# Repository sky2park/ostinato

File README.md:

# Ostinato

[🇺🇸 English](docs/README.en.md)

처음부터 직접 설계한 40% 오소리니어 기계식 키보드입니다.

Ostinato는 커스텀 PCB, 알루미늄 케이스, 가스켓 마운트 플레이트, 로터리 엔코더, RGB 상태 표시등, USB 연결을 기본으로 하는 45키 오소리니어 키보드입니다. USB 전원이 공급되는 상태에서 Bluetooth 무선 출력을 사용할 수 있습니다.

이 프로젝트에는 PCB와 케이스부터 QMK/Vial 펌웨어와 ESP32-C3 Bluetooth 컨트롤러까지 전체 하드웨어 및 펌웨어 설계가 포함되어 있습니다.

---

## 주요 기능

- 40% 오소리니어 레이아웃
- 45키
- MX 호환 스위치
- QMK 펌웨어
- Vial 지원
- USB 및 Bluetooth 연결
- ESP32-C3 기반 Bluetooth 컨트롤러 (USB 전원 필요, 배터리 없음, 단독 무선 작동 불가)
- RP2040 기반 메인 컨트롤러
- 3개의 Bluetooth 연결 슬롯
- 로터리 엔코더
- SK6812MINI RGB LED
- 전용 Bluetooth 상태 표시등
- 레이어 상태 표시
- 가스켓 마운트 플레이트
- 커스텀 알루미늄 상판 케이스
- MJF PA12S 나일론 하판 케이스
- SUS304 스테인리스 스틸 또는 H59 구리 합금 황동 내부 웨이트

---

## 사양

| 항목 | 내용 |
|---|---|
| 레이아웃 | 40% 오소리니어 |
| 키 수 | 45 |
| 메인 MCU | RP2040 |
| Bluetooth MCU | ESP32-C3 |
| 펌웨어 | QMK |
| 키맵 설정 | Vial |
| 연결 방식 | USB 기본 / Bluetooth 무선 출력 (USB 전원 필요) |
| 전원 공급 | USB |
| 배터리 | 없음 |
| Bluetooth 슬롯 | 3 |
| 스위치 종류 | MX 호환 |
| RGB LED | SK6812MINI (4개) |
| 로터리 엔코더 | 1개 |
| 마운팅 | 가스켓 마운트 (Poron) |
| 플레이트 | PC |
| 상판 케이스 | 6061 알루미늄 |
| 하판 케이스 | MJF PA12S 나일론 |
| 내부 웨이트 | SUS304 스테인리스 스틸 또는 H59 구리 합금 황동 |

---

## 레이아웃

Ostinato는 45키의 컴팩트한 40% 오소리니어 레이아웃을 사용합니다.

작은 크기를 유지하면서 풀사이즈 키보드에 준하는 기능을 제공할 수 있도록 여러 레이어를 중심으로 설계되었습니다.

### 레이어

펌웨어에는 다음과 같은 주요 레이어가 포함되어 있습니다:

- **기본**
- **내비게이션**
- **숫자 / 기호**
- **기능**
- **게이밍**
- **게이밍+**
- **게이밍 내비게이션**

추가 레이어와 키 할당은 Vial을 통해 설정할 수 있습니다.

---

## 연결

Ostinato는 USB 연결을 기본으로 사용하며, USB 전원이 공급되는 상태에서 Bluetooth 무선 출력을 지원합니다.

> **⚠️ 전원 및 Bluetooth 사용 안내**
>
> Ostinato는 배터리를 내장하지 않은 키보드입니다. 키보드의 작동과 Bluetooth 사용을 위해 USB 케이블을 연결해야 합니다.
>
> USB 케이블을 연결하지 않은 상태에서는 키보드 단독으로 Bluetooth를 사용할 수 없습니다.

RP2040은 키보드의 주요 기능을 담당하며, ESP32-C3 모듈이 Bluetooth 연결을 제공합니다.

### USB

USB 모드에서는 일반적인 USB HID 키보드로 동작합니다.

### Bluetooth

키보드는 3개의 Bluetooth 연결 슬롯을 지원합니다:

- **Bluetooth 1**
- **Bluetooth 2**
- **Bluetooth 3**

활성 Bluetooth 슬롯은 키보드에서 직접 선택할 수 있습니다. 펌웨어는 UART를 통해 ESP32-C3와 통신하며 Bluetooth 연결 상태와 슬롯 선택을 제어합니다.

Bluetooth를 사용하더라도 USB 케이블을 통한 전원 공급이 필요합니다. 배터리가 없으므로 USB 전원 없이 Bluetooth만으로 작동할 수 없습니다.

---

## Bluetooth 상태

RGB LED는 Bluetooth 상태를 시각적으로 표시하는 데 사용됩니다. 각 Bluetooth 슬롯에는 전용 상태 표시등이 있습니다.

표시등은 다음과 같은 상태를 구분합니다:

- 광고(Advertising)
- 연결됨
- 페어링
- 오류 / 사용 불가

이를 통해 호스트 기기를 사용하지 않고도 현재 Bluetooth 연결 상태를 확인할 수 있습니다.

---

## RGB 표시등

Ostinato는 4개의 SK6812MINI RGB LED를 사용합니다. 이 LED는 장식용 백라이트가 아니라 기능적인 상태 표시등으로 사용됩니다.

### Bluetooth 표시등

3개의 LED가 각각 3개의 Bluetooth 슬롯 상태를 표시합니다.

### 레이어 표시등

나머지 1개의 LED는 레이어/상태 표시용으로 사용됩니다. 펌웨어는 이 표시등을 특수 키보드 기능의 상태를 표시하는 데에도 사용할 수 있습니다.

---

## 로터리 엔코더

Ostinato에는 추가 입력을 위한 로터리 엔코더가 포함되어 있습니다.

엔코더는 QMK와 Vial을 통해 설정할 수 있으며, 활성 레이어에 따라 서로 다른 기능을 할당할 수 있습니다.

---

## 아키텍처 및 설계 철학

Ostinato의 목표는 컴팩트한 오소리니어 레이아웃에 일반적으로 대형 키보드에서 제공되는 기능을 결합하는 것입니다.

하나의 무선 컨트롤러에 모든 기능을 의존하는 대신, 메인 키보드 컨트롤러와 Bluetooth 컨트롤러를 분리하는 구조로 설계했습니다:

```text
       ┌───────────────┐
       │    RP2040     │
       │ Main Keyboard │
       │  Controller   │
       └───────┬───────┘
               │
              UART
               │
       ┌───────▼───────┐
       │   ESP32-C3    │
       │   Bluetooth   │
       │  Controller   │
       └───────────────┘
```

이 아키텍처를 통해 RP2040은 핵심 키보드 동작(매트릭스 스캔, 조명, Vial 설정)을 담당하고, ESP32-C3는 Bluetooth 연결 스택을 담당합니다.

---

## 펌웨어

Ostinato 펌웨어는 QMK 및 Vial-QMK를 기반으로 하며 **GNU General Public License v2.0 (GPL-2.0)**에 따라 라이선스가 부여됩니다.

```text
firmware/
├── esp32-c3/
├── qmk/
│   └── ostinato/
└── vial/
    └── ostinato/
```

- **QMK 펌웨어**: 매트릭스 스캔, 키맵 및 레이어, 커스텀 키코드, 로터리 엔코더, RGB 상태 표시등, USB 출력, ESP32-C3와의 UART 통신을 담당합니다.
- **ESP32-C3 펌웨어**: Bluetooth 프로파일 관리, 연결 슬롯, 무선 HID 출력을 담당합니다.

### 커스텀 키코드

Ostinato는 출력 및 연결 제어를 위해 다음과 같은 커스텀 키코드를 정의합니다:

- `OUT_USB`
- `OUT_BT1`
- `OUT_BT2`
- `OUT_BT3`
- `BT_CLR`

이 키코드를 사용하면 USB와 페어링된 3개의 Bluetooth 기기 사이를 즉시 전환할 수 있습니다.

---

## 하드웨어

PCB, 케이스, 플레이트 및 관련 CAD 파일을 포함한 Ostinato 하드웨어 설계 파일은 **Creative Commons Attribution-NonCommercial 4.0 International (CC BY-NC 4.0)** 라이선스에 따라 제공됩니다.

개인적 및 비상업적 사용은 허용됩니다.

상업적 사용에는 저작자의 사전 허가가 필요합니다.

하드웨어는 다음과 같은 모듈형 커스텀 보드로 구성됩니다:

```text
pcb/
├── main-module/
├── led_module/
└── knob-module/
```

- **메인 모듈**: RP2040 컨트롤러, ESP32-C3, 다이오드 매트릭스 및 전원 회로를 탑재합니다.
- **LED 모듈**: 슬롯 및 레이어 상태 표시를 위한 4개의 SK6812MINI 어드레서블 RGB LED를 탑재합니다.
- **노브 모듈**: 로터리 엔코더와 브레이크아웃 인터페이스를 탑재합니다.

### 케이스 및 플레이트

- **상판 케이스**: CNC 가공 6061 알루미늄
- **하판 케이스**: MJF 3D 프린팅 PA12S 나일론
- **내부 웨이트**: 레이저 절단 SUS304 스테인리스 스틸 또는 H59 구리 합금 황동
- **마운팅**: PC 플레이트를 분리하는 커스텀 Poron 가스켓 스트립을 사용하여 부드럽고 공명감 있는 바텀아웃을 구현합니다.

> **제조 및 공차 관련 참고사항**  
> 모든 케이스 부품(상판 케이스, 하판 케이스, 내부 웨이트)은 **JLCCNC** 및 **JLC3DP**를 통해 프로토타입을 제작하고 검증했습니다. 제조업체와 제작 방식에 따라 공차와 표면 마감이 달라질 수 있으므로, 다른 업체에서 제작한 부품은 테스트되지 않았으며 조립 또는 치수 호환성 문제가 발생할 수 있습니다.

플레이트 절단 프로파일은 `plate/` 아래에 DXF 형식으로 제공됩니다:
- `design.dxf`
- `plate.dxf`

---

## 제조 및 주문 가이드

모든 부품은 특정 제작 업체를 기준으로 설계하고 검증했습니다. Ostinato를 제작할 계획이라면 아래 주문 가이드를 참고하세요.

### 개요

| 부품 | 소스 파일 | 권장 서비스 | 공정 / 재료 사양 |
|---|---|---|---|
| **Top Case** | `case/top.step`<br>`case/top_theads.pdf` (Thread/tapping drawing) | JLCCNC | CNC Machining / 6061 Aluminum (Sandblasted / Anodized) |
| **Bottom Case** | `case/bottom.step` | JLC3DP | 3D Printing / MJF Nylon (PA12S) |
| **Internal Weight** | `case/weight.step` | JLCCNC | CNC or Sheet Metal / SUS304 Stainless steel or H59 Brass |
| **Plate** | `plate/plate.dxf` | Laser cutting service | Laser Cut / 1.5mm Polycarbonate (PC) |
| **PCBs** | `pcb/*/gerber/` | JLCPCB | FR-4 / 1.6mm (or 1.2mm depending on build) |

---

### 부품 상세 및 주문 방법

#### 1. 케이스 및 웨이트 (JLCCNC / JLC3DP)
- **Top Case**:
  - **File**: `case/top.step`
  - **나사산 도면**: `case/top_theads.pdf` (탭 가공을 주문할 때 이 2D 도면을 함께 첨부하세요)
  - **서비스**: [JLCCNC](https://jlccnc.com/) (CNC 가공)
  - **재료**: 6061 알루미늄
  - **표면 처리**: 비드 블라스트(샌드블라스트 #150 또는 #180) + 아노다이징(원하는 색상)
- **Bottom Case**:
  - **File**: `case/bottom.step`
  - **Service**: [JLC3DP](https://jlc3dp.com/) (3D Printing)
  - **기술**: MJF (Multi Jet Fusion)
  - **재료**: PA12S 나일론 (검정/염색)
- **Internal Weight**:
  - **File**: `case/weight.step`
  - **Service**: [JLCCNC](https://jlccnc.com/)
  - **재료**: SUS304 스테인리스 스틸 (헤어라인 / 샌드블라스트) 또는 H59 황동

> ⚠️ **중요 공차 경고**:  
> CAD 모델, 공차 및 조립 여유 치수는 **JLCCNC** 및 **JLC3DP**를 기준으로 조정하고 검증했습니다. 다른 업체나 다른 제작 방식은 테스트되지 않았으며, 부적절한 조립, 수축 편차 또는 조립 문제가 발생할 수 있습니다.

#### 2. 스위치 플레이트
- **File**: `plate/plate.dxf`
- **재료**: 1.5mm 폴리카보네이트 (PC)
- **서비스**: 정밀 레이저 절단이 가능한 업체 (예: JLCCNC 판재 절단 또는 현지 레이저 절단 업체).

#### 3. PCB
- **Paths**:
  - `pcb/main-module/`
  - `pcb/led_module/`
  - `pcb/knob-module/`
- **Service**: [JLCPCB](https://jlcpcb.com/)
- **Ordering Recommendations**:
  - Upload the Gerber zip files along with the **BOM and CPL files** from each folder to order the **PCB Assembly (SMT)** service.
  - **PCBA Settings**:
    - **Assembly Side**: Select **`Bottom Side`** for all three modules.
    - **PCBA Type**:
      - `main-module`: Must be set to **`Standard`** due to assembly constraints of the ESP32-C3 module (bottom pad soldering).
      - `led_module` & `knob-module`: Select **`Economy`**.
  - ⚠️ **Note**: The **EC11 rotary encoder** on the `knob-module` is not covered by the SMT service; source it separately and solder it by hand (through-hole soldering).
  
#### 4. 추가 기성 부품 (하드웨어 및 구매)

이러한 표준 하드웨어 부품과 구성품은 별도 제작품이 아니며, 일반 하드웨어 마켓플레이스(예: AliExpress)나 커스텀 키보드 판매처에서 구매할 수 있습니다.

> **참고**: 아래 링크는 제가 프로토타입 제작에 실제로 사용한 동일한 제품 목록과 구매처입니다. 참고용으로만 제공하며, 사양에 맞는 동등한 부품이라면 어떤 제품을 사용해도 됩니다.

| 품목 | 사양 | 수량 | 참고 링크 | 비고 |
|---|---|---|---|---|
| **Poron Gasket Strips** | 20mm (L) × 3mm (W) × 2mm (T) | 8 | [AliExpress](https://ko.aliexpress.com/item/1005005713921230.html) | Mounts to plate tabs / case edges |
| **FPC Ribbon Cable** | 0.5mm pitch, 6-pin, **Reverse (Type B)**, 10–15cm | 2 | [AliExpress](https://aliexpress.com/item/1005007862185591.html) | Connects main module to LED / knob modules |
| **Rotary Encoder** | EC11 rotary encoder, **15mm shaft height** | 1 | [AliExpress](https://aliexpress.com/item/1005009120433387.html) | Hand-soldered onto `knob-module` |
| **Encoder Knob** | Compatible with EC11 shaft **20 x 13 x 6mm** | 1 | [AliExpress](https://aliexpress.com/item/1005007339301144.html) | Fits selected rotary encoder |
| **Unified Daughterboard S1 & Cable** | Unified Daughterboard (UDB) S1 with Molex cable | 1 | [Vendor Link](https://keebd.com/products/unified-daughterboards?variant=45606739411096) | Available via various keyboard vendor stores (e.g., CannonKeys, Swagkeys, etc.)
| **Light Guides** | Acrylic light pipe / guide **1.5-2.2 or 2.9-3.0** | 4 | [AliExpress](https://aliexpress.com/item/1005005231503928.html) | Diffuses status LEDs |
| **Heat-set Insert** | M2 × L3mm × OD 3.2mm | 4 | [AliExpress](https://aliexpress.com/item/1005006472641726.html) | Case / module mounting |
| **Heat-set Insert** | M3 × L4mm × OD 4.2mm | 6 | [AliExpress](https://aliexpress.com/item/1005006472641726.html) | Weight / case and Weight / UDB mounting |
| **Screw** | M2 × 4mm | 4 | [AliExpress](https://aliexpress.com/item/1005005270702287.html) | Internal module mounting |
| **Screw** | M2.5 × 8mm | 4 | [AliExpress](https://aliexpress.com/item/1005005270702287.html) | Case assembly |
| **Screw** | M3 × 5mm | 6 | [AliExpress](https://aliexpress.com/item/1005005270702287.html) | Internal weight / UDB fastening |

---

## 빌드 가이드

🚧 상세 빌드 가이드 영상은 현재 준비 중입니다.

---

## 저장소 구조

```text
ostinato/
├── case/             # CAD and step/stl files for case parts
├── firmware/
│   ├── esp32-c3/     # ESP-IDF / Arduino BT firmware
│   ├── qmk/          # QMK source and keyboard rules
│   │   └── ostinato/
│   └── vial/         # Vial configuration & keymap files
│       └── ostinato/
├── pcb/
│   ├── main-module/  # Schematic, KiCad layouts, and Gerber files
│   ├── led_module/
│   └── knob-module/
├── plate/
│   ├── design.dxf
│   └── plate.dxf
└── README.md
```

---

## 상태

Ostinato는 현재 개발이 진행 중인 커스텀 하드웨어 프로젝트입니다. 실제 리비전을 테스트하는 과정에서 회로도, Gerber 파일 및 펌웨어 구현이 호환성을 깨뜨리는 형태로 변경될 수 있습니다.

---

## 크레딧

**sky2park**가 설계 및 개발했습니다.

- [QMK Firmware](https://qmk.fm/)
- [Vial](https://get.vial.today/)
- Raspberry Pi RP2040 & Espressif ESP32-C3

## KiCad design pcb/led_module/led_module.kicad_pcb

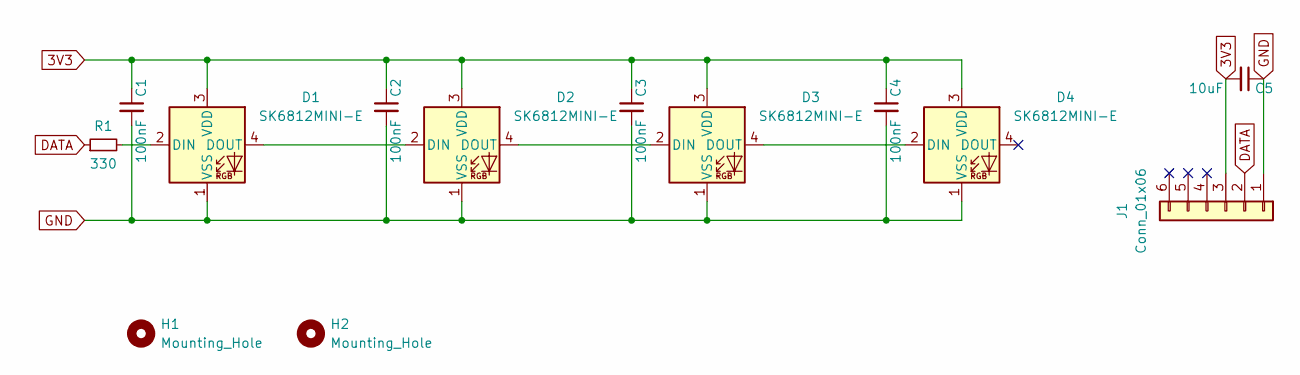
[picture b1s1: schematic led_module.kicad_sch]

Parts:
C1, C2, C3, C4: 100nF; C_0402_1005Metric; LCSC C66501
C5: 10uF; C_0402_1005Metric; LCSC C66501
D1, D2, D3, D4: SK6812MINI-E; LED_SK6812MINI-E_3.2x2.8mm_P1.5mm_ReverseMount
H1, H2: Mounting_Hole; Standoff_M2x6mm
J1: Conn_01x06; Hirose_FH12-6S-0.5SH_1x06-1MP_P0.50mm_Horizontal
R1: 330; R_0402_1005Metric; LCSC C21190

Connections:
3V3: C1.1, C2.1, C3.1, C4.1, C5.2, D1.3 (VDD), D2.3 (VDD), D3.3 (VDD), D4.3 (VDD), J1.3
DATA: J1.2, R1.1
GND: C1.2, C2.2, C3.2, C4.2, C5.1, D1.1 (VSS), D2.1 (VSS), D3.1 (VSS), D4.1 (VSS), J1.1
unnamed: D1.2 (DIN), R1.2
unnamed: D1.4 (DOUT), D2.2 (DIN)
unnamed: D2.4 (DOUT), D3.2 (DIN)
unnamed: D3.4 (DOUT), D4.2 (DIN)

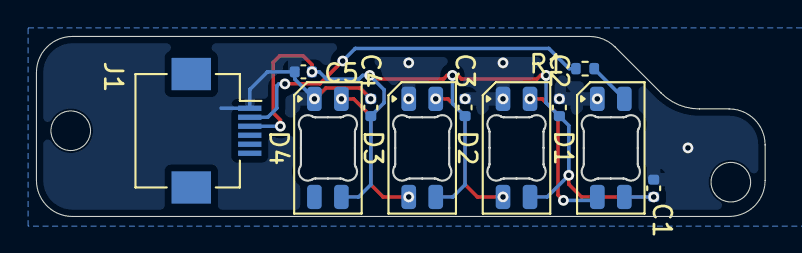
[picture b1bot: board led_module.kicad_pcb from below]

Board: 2 copper layers, 40.5 x 10.0 mm, 13 parts (11 on the bottom side), 7 nets.

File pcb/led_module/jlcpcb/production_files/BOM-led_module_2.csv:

Comment,Designator,Footprint,LCSC,Quantity
100nF,"C1,C2,C3,C4",C_0402_1005Metric,C1525,4
10uF,C5,C_0402_1005Metric,C15525,1
330,R1,R_0402_1005Metric,C21190,1
Conn_01x06,J1,Hirose_FH12-6S-0.5SH_1x06-1MP_P0.50mm_Horizontal,C202118,1
SK6812MINI-E,"D1,D2,D3,D4",LED_SK6812MINI-E_3.2x2.8mm_P1.5mm_ReverseMount,C5378731,4

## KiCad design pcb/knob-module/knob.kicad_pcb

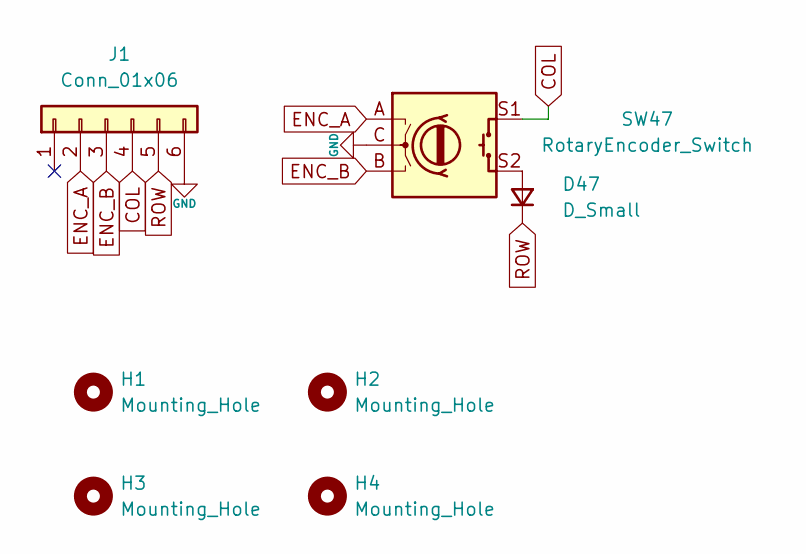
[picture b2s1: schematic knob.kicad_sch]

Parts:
D47: D_Small; D_SOD-123
H1, H2, H3, H4: Mounting_Hole; Standoff_M2x6mm
J1: Conn_01x06; Hirose_FH12-6S-0.5SH_1x06-1MP_P0.50mm_Horizontal
SW47: RotaryEncoder_Switch; Encoder_EC11_MX

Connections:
COL: J1.4, SW47.S1
ENC_A: J1.2, SW47.A
ENC_B: J1.3, SW47.B
GND: J1.6, SW47.C
unnamed: D47.2 (A), SW47.S2
ROW: D47.1 (K), J1.5

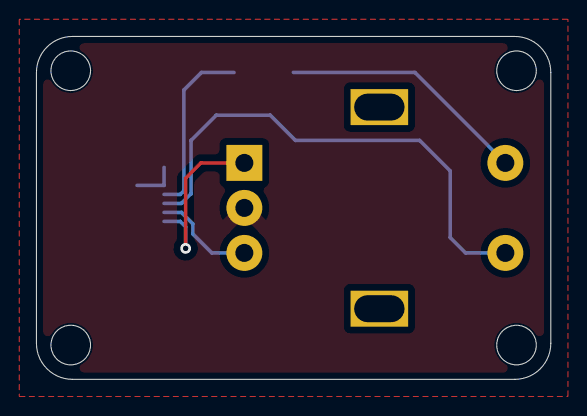
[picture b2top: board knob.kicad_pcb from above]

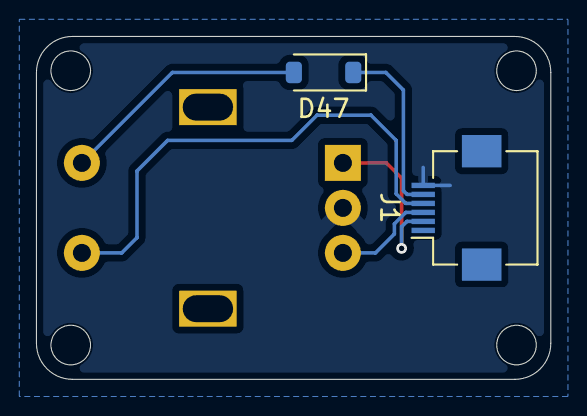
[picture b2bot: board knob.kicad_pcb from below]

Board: 2 copper layers, 28.6 x 19.1 mm, 7 parts (2 on the bottom side), 6 nets.

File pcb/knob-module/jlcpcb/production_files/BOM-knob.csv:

Comment,Designator,Footprint,LCSC,Quantity
Conn_01x06,J1,Hirose_FH12-6S-0.5SH_1x06-1MP_P0.50mm_Horizontal,C202118,1
D_Small,D47,D_SOD-123,C81598,1

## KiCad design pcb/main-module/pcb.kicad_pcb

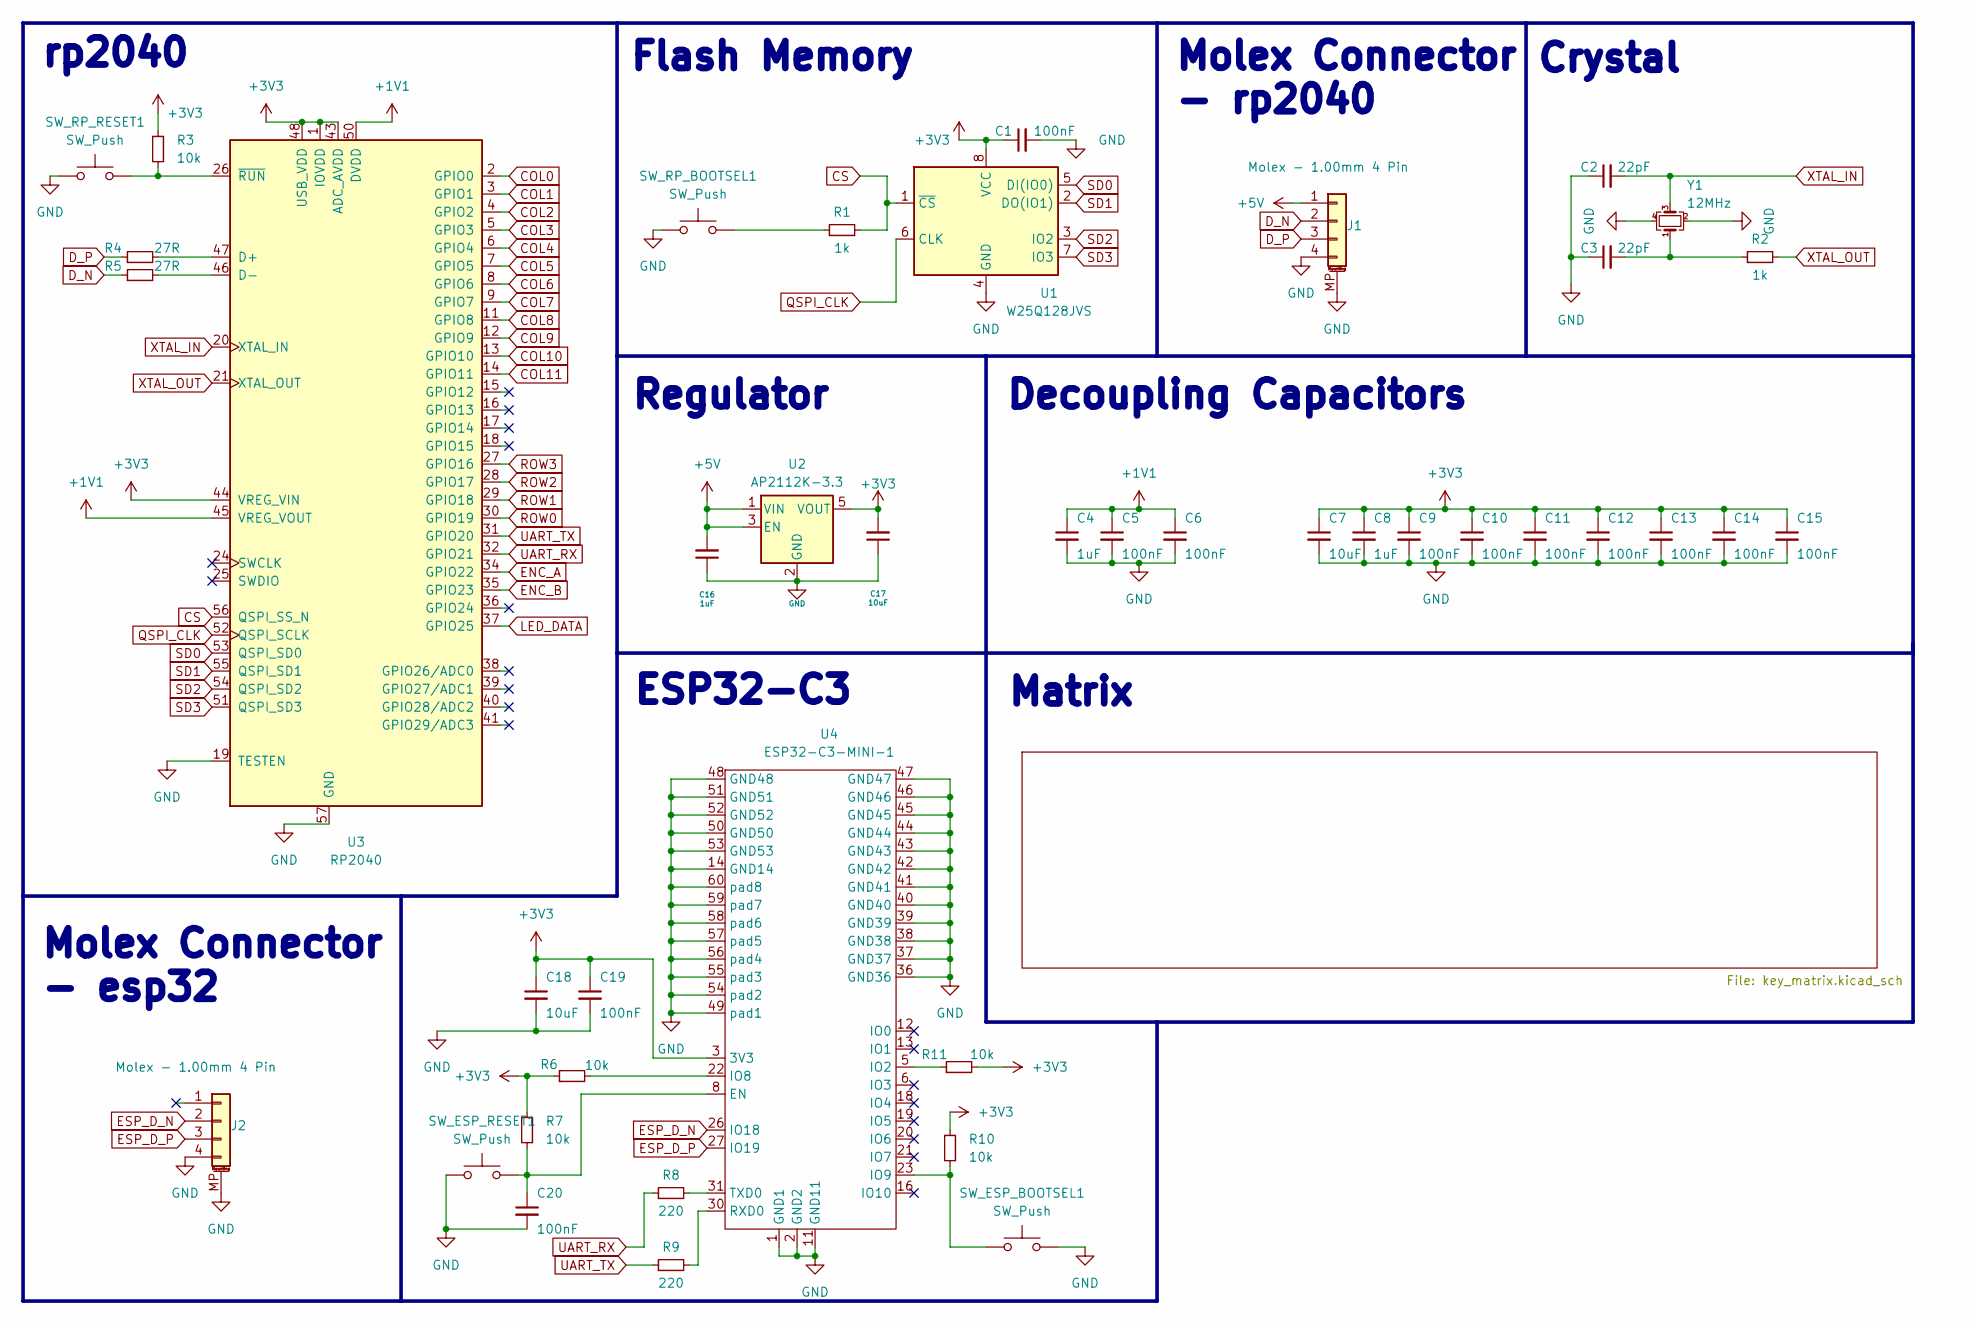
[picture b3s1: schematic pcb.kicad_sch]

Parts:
C1, C5, C6, C9, C10, C11, C12, C13, C14, C15: 100nF; C_0402_1005Metric; LCSC C66501
C2, C3: 22pF; C_0402_1005Metric; LCSC C1653
C4, C8, C16: 1uF; C_0402_1005Metric; LCSC C5673
C7: 10uF; C_0402_1005Metric; LCSC C1691
C17: 10uF; C_0402_1005Metric; LCSC C19702
C18: 10uF; C_0402_1005Metric; LCSC C15525
C19, C20: 100nF; C_0402_1005Metric; LCSC C1525
J1: Molex - 1.00mm 4 Pin; Molex_Pico-EZmate_78171-0004_1x04-1MP_P1.20mm_Vertical; LCSC C588524
J2: Molex - 1.00mm 4 Pin; Molex_Pico-EZmate_78171-0004_1x04-1MP_P1.20mm_Vertical; LCSC C160404
R1, R2: 1k; R_0402_1005Metric; LCSC C21190
R3: 10k; R_0402_1005Metric; LCSC C25804
R4, R5: 27R; R_0402_1005Metric; LCSC C25190
R6, R7, R10, R11: 10k; R_0402_1005Metric; LCSC C11702
R8, R9: 220; R_0402_1005Metric
SW_ESP_BOOTSEL1: SW_Push; SW_SPST_TS-1088-xR020
SW_ESP_RESET1: SW_Push; SW_SPST_TS-1088-xR020
SW_RP_BOOTSEL1: SW_Push; SW_SPST_TS-1088-xR020
SW_RP_RESET1: SW_Push; SW_SPST_TS-1088-xR020
U1: W25Q128JVS; SOIC-8_5.3x5.3mm_P1.27mm; LCSC C131025
U2: AP2112K-3.3; SOT-23-5
U3: RP2040; RP2040-QFN-56; LCSC C2040
U4: ESP32-C3-MINI-1; LCSC C41349510
Y1: 12MHz; Crystal_SMD_3225-4Pin_3.2x2.5mm; LCSC C9002

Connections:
+1V1: C4.1, C5.1, C6.1, U3.23 (DVDD), U3.45 (VREG_VOUT), U3.50 (DVDD)
+3V3: C1.1, C7.1, C8.1, C9.1, C10.1, C11.1, C12.1, C13.1, C14.1, C15.1, C17.2, C18.1, C19.1, R3.1, R6.1, R7.1, R10.1, R11.2, U1.8 (VCC), U2.5 (VOUT), U3.1 (IOVDD), U3.10 (IOVDD), U3.22 (IOVDD), U3.33 (IOVDD), U3.42 (IOVDD), U3.43 (ADC_AVDD), U3.44 (VREG_VIN), U3.48 (USB_VDD), U3.49 (IOVDD), U4.3 (3V3); also elsewhere on the board
+5V: C16.2, J1.1, U2.1 (VIN), U2.3 (EN)
COL0: U3.2 (GPIO0); also elsewhere on the board
COL1: U3.3 (GPIO1); also elsewhere on the board
COL2: U3.4 (GPIO2); also elsewhere on the board
COL3: U3.5 (GPIO3); also elsewhere on the board
COL4: U3.6 (GPIO4); also elsewhere on the board
COL5: U3.7 (GPIO5); also elsewhere on the board
COL6: U3.8 (GPIO6); also elsewhere on the board
COL7: U3.9 (GPIO7); also elsewhere on the board
COL8: U3.11 (GPIO8); also elsewhere on the board
COL9: U3.12 (GPIO9); also elsewhere on the board
COL10: U3.13 (GPIO10); also elsewhere on the board
COL11: U3.14 (GPIO11); also elsewhere on the board
CS: R1.2, U1.1 (~CS), U3.56 (QSPI_SS_N)
D_N: J1.2, R5.1
D_P: J1.3, R4.1
ENC_A: U3.34 (GPIO22); also elsewhere on the board
ENC_B: U3.35 (GPIO23); also elsewhere on the board
ESP_D_N: J2.2, U4.26 (IO18)
ESP_D_P: J2.3, U4.27 (IO19)
GND: C1.2, C2.1, C3.1, C4.2, C5.2, C6.2, C7.2, C8.2, C9.2, C10.2, C11.2, C12.2, C13.2, C14.2, C15.2, C16.1, C17.1, C18.2, C19.2, C20.2, J1.4, J1.MP (MountPin), J2.4, J2.MP (MountPin), SW_ESP_BOOTSEL1.2, SW_ESP_RESET1.1, SW_RP_BOOTSEL1.1, SW_RP_RESET1.1, U1.4 (GND), U2.2 (GND), U3.19 (TESTEN), U3.57 (GND), U4.1 (GND1), U4.2 (GND2), U4.11 (GND11), U4.14 (GND14), U4.36 (GND36), U4.37 (GND37), U4.38 (GND38), U4.39 (GND39), U4.40 (GND40), U4.41 (GND41), U4.42 (GND42), U4.43 (GND43), U4.44 (GND44), U4.45 (GND45), U4.46 (GND46), U4.47 (GND47), U4.48 (GND48), U4.49 (pad1), U4.50 (GND50), U4.51 (GND51), U4.52 (GND52), U4.53 (GND53), U4.54 (pad2), U4.55 (pad3), U4.56 (pad4), U4.57 (pad5), U4.58 (pad6), U4.59 (pad7), U4.60 (pad8), Y1.2, Y1.4; also elsewhere on the board
LED_DATA: U3.37 (GPIO25); also elsewhere on the board
unnamed: C3.2, R2.1, Y1.1
unnamed: R1.1, SW_RP_BOOTSEL1.2
unnamed: R4.2, U3.47 (D+)
unnamed: R5.2, U3.46 (D-)
unnamed: R3.2, SW_RP_RESET1.2, U3.26 (~RUN)
unnamed: C20.1, R7.2, SW_ESP_RESET1.2, U4.8 (EN)
unnamed: R11.1, U4.5 (IO2)
unnamed: R6.2, U4.22 (IO8)
unnamed: R10.2, SW_ESP_BOOTSEL1.1, U4.23 (IO9)
unnamed: R9.2, U4.30 (RXD0)
unnamed: R8.2, U4.31 (TXD0)
QSPI_CLK: U1.6 (CLK), U3.52 (QSPI_SCLK)
ROW0: U3.30 (GPIO19); also elsewhere on the board
ROW1: U3.29 (GPIO18); also elsewhere on the board
ROW2: U3.28 (GPIO17); also elsewhere on the board
ROW3: U3.27 (GPIO16); also elsewhere on the board
SD0: U1.5 (DI(IO0)), U3.53 (QSPI_SD0)
SD1: U1.2 (DO(IO1)), U3.55 (QSPI_SD1)
SD2: U1.3 (IO2), U3.54 (QSPI_SD2)
SD3: U1.7 (IO3), U3.51 (QSPI_SD3)
UART_RX: R8.1, U3.32 (GPIO21)
UART_TX: R9.1, U3.31 (GPIO20)
XTAL_IN: C2.2, U3.20 (XTAL_IN), Y1.3
XTAL_OUT: R2.2, U3.21 (XTAL_OUT)

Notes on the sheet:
Molex Connector - rp2040
Decoupling Capacitors
Regulator
rp2040
Crystal
ESP32-C3
Molex Connector - esp32
Flash Memory
Matrix

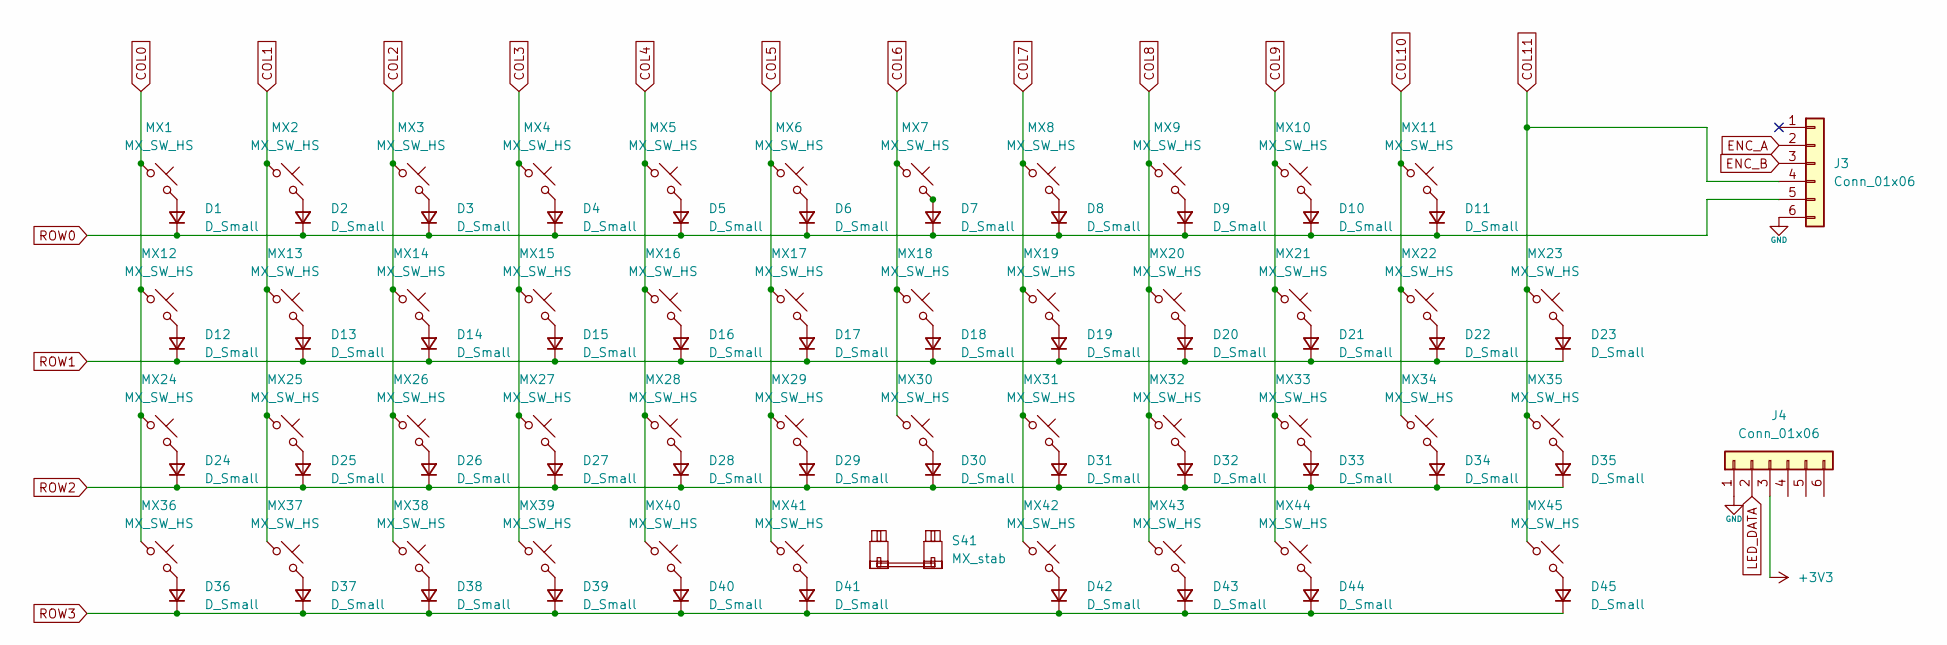
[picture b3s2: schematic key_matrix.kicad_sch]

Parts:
D1, D2, D3, D4, D5, D6, D7, D8, D9, D10, D11, D12, D13, D14, D15, D16, D17, D18, D19, D20, D21, D22, D23, D24, D25, D26, D27, D28, D29, D30, D31, D32, D33, D34, D35, D36, D37, D38, D39, D40, D41, D42, D43, D44, D45: D_Small; D_SOD-123
J3, J4: Conn_01x06; Hirose_FH12-6S-0.5SH_1x06-1MP_P0.50mm_Horizontal
MX1, MX2, MX3, MX4, MX5, MX6, MX7, MX8, MX9, MX10, MX11, MX12, MX13, MX14, MX15, MX16, MX17, MX18, MX19, MX20, MX21, MX22, MX23, MX24, MX25, MX26, MX27, MX28, MX29, MX30, MX31, MX32, MX33, MX34, MX35, MX36, MX37, MX38, MX39, MX40, MX41, MX42, MX43, MX44, MX45: MX_SW_HS; SW_MX_HS_CPG151101S11_1u
S41: MX_stab; STAB_MX_P_2u

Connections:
+3V3: J4.3; also elsewhere on the board
COL0: MX1.1, MX12.1, MX24.1, MX36.1; also elsewhere on the board
COL1: MX2.1, MX13.1, MX25.1, MX37.1; also elsewhere on the board
COL2: MX3.1, MX14.1, MX26.1, MX38.1; also elsewhere on the board
COL3: MX4.1, MX15.1, MX27.1, MX39.1; also elsewhere on the board
COL4: MX5.1, MX16.1, MX28.1, MX40.1; also elsewhere on the board
COL5: MX6.1, MX17.1, MX29.1, MX41.1; also elsewhere on the board
COL6: MX7.1, MX18.1, MX30.1; also elsewhere on the board
COL7: MX8.1, MX19.1, MX31.1, MX42.1; also elsewhere on the board
COL8: MX9.1, MX20.1, MX32.1, MX43.1; also elsewhere on the board
COL9: MX10.1, MX21.1, MX33.1, MX44.1; also elsewhere on the board
COL10: MX11.1, MX22.1, MX34.1; also elsewhere on the board
COL11: J3.4, MX23.1, MX35.1, MX45.1; also elsewhere on the board
ENC_A: J3.2; also elsewhere on the board
ENC_B: J3.3; also elsewhere on the board
GND: J3.6, J4.1; also elsewhere on the board
LED_DATA: J4.2; also elsewhere on the board
unnamed: D1.2 (A), MX1.2
unnamed: D2.2 (A), MX2.2
unnamed: D3.2 (A), MX3.2
unnamed: D4.2 (A), MX4.2
unnamed: D5.2 (A), MX5.2
unnamed: D6.2 (A), MX6.2
unnamed: D7.2 (A), MX7.2
unnamed: D8.2 (A), MX8.2
unnamed: D9.2 (A), MX9.2
unnamed: D10.2 (A), MX10.2
unnamed: D11.2 (A), MX11.2
unnamed: D12.2 (A), MX12.2
unnamed: D13.2 (A), MX13.2
unnamed: D14.2 (A), MX14.2
unnamed: D15.2 (A), MX15.2
unnamed: D16.2 (A), MX16.2
unnamed: D17.2 (A), MX17.2
unnamed: D18.2 (A), MX18.2
unnamed: D19.2 (A), MX19.2
unnamed: D20.2 (A), MX20.2
unnamed: D21.2 (A), MX21.2
unnamed: D22.2 (A), MX22.2
unnamed: D23.2 (A), MX23.2
unnamed: D24.2 (A), MX24.2
unnamed: D25.2 (A), MX25.2
unnamed: D26.2 (A), MX26.2
unnamed: D27.2 (A), MX27.2
unnamed: D28.2 (A), MX28.2
unnamed: D29.2 (A), MX29.2
unnamed: D30.2 (A), MX30.2
unnamed: D31.2 (A), MX31.2
unnamed: D32.2 (A), MX32.2
unnamed: D33.2 (A), MX33.2
unnamed: D34.2 (A), MX34.2
unnamed: D35.2 (A), MX35.2
unnamed: D36.2 (A), MX36.2
unnamed: D37.2 (A), MX37.2
unnamed: D38.2 (A), MX38.2
unnamed: D39.2 (A), MX39.2
unnamed: D40.2 (A), MX40.2
unnamed: D41.2 (A), MX41.2
unnamed: D42.2 (A), MX42.2
unnamed: D43.2 (A), MX43.2
unnamed: D44.2 (A), MX44.2
unnamed: D45.2 (A), MX45.2
ROW0: D1.1 (K), D2.1 (K), D3.1 (K), D4.1 (K), D5.1 (K), D6.1 (K), D7.1 (K), D8.1 (K), D9.1 (K), D10.1 (K), D11.1 (K), J3.5; also elsewhere on the board
ROW1: D12.1 (K), D13.1 (K), D14.1 (K), D15.1 (K), D16.1 (K), D17.1 (K), D18.1 (K), D19.1 (K), D20.1 (K), D21.1 (K), D22.1 (K), D23.1 (K); also elsewhere on the board
ROW2: D24.1 (K), D25.1 (K), D26.1 (K), D27.1 (K), D28.1 (K), D29.1 (K), D30.1 (K), D31.1 (K), D32.1 (K), D33.1 (K), D34.1 (K), D35.1 (K); also elsewhere on the board
ROW3: D36.1 (K), D37.1 (K), D38.1 (K), D39.1 (K), D40.1 (K), D41.1 (K), D42.1 (K), D43.1 (K), D44.1 (K), D45.1 (K); also elsewhere on the board

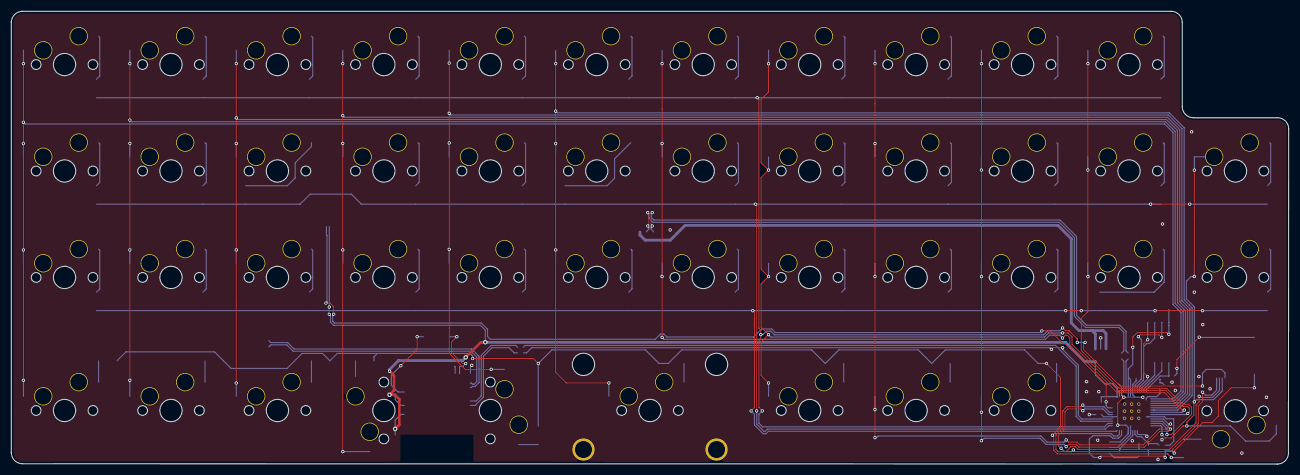
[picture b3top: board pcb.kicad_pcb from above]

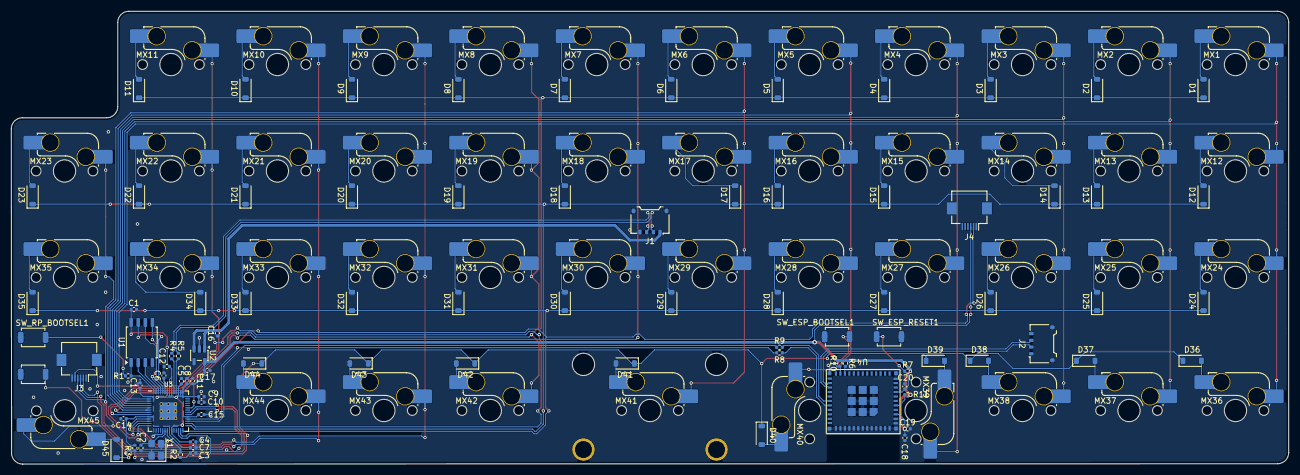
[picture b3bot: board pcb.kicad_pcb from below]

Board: 2 copper layers, 228.6 x 81.0 mm, 135 parts (134 on the bottom side), 93 nets.

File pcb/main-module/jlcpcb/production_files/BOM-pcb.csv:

Comment,Designator,Footprint,LCSC,Quantity
100nF,"C1,C10,C11,C12,C13,C14,C15,C19,C20,C5,C6,C9",C_0402_1005Metric,C1525,12
10k,"R10,R11,R3,R6,R7",R_0402_1005Metric,C25744,5
10uF,"C17,C18,C7",C_0402_1005Metric,C15525,3
12MHz,Y1,Crystal_SMD_3225-4Pin_3.2x2.5mm,C9002,1
1k,"R1,R2",R_0402_1005Metric,C11702,2
1uF,"C16,C4,C8",C_0402_1005Metric,C52923,3
220,"R8,R9",R_0402_1005Metric,C25091,2
22pF,"C2,C3",C_0402_1005Metric,C1555,2
27R,"R4,R5",R_0402_1005Metric,C25100,2
AP2112K-3.3,U2,SOT-23-5,C3021085,1
Conn_01x06,"J3,J4",Hirose_FH12-6S-0.5SH_1x06-1MP_P0.50mm_Horizontal,C202118,2
D_Small,"D1,D10,D11,D12,D13,D14,D15,D16,D17,D18,D19,D2,D20,D21,D22,D23,D24,D25,D26,D27,D28,D29,D3,D30,D31,D32,D33,D34,D35,D36,D37,D38,D39,D4,D40,D41,D42,D43,D44,D45,D5,D6,D7,D8,D9",D_SOD-123,C81598,45
ESP32-C3-MINI-1,U4,ESP32-C3-MINI-1,C2838502,1
Molex - 1.00mm 4 Pin,"J1,J2",Molex_Pico-EZmate_78171-0004_1x04-1MP_P1.20mm_Vertical,C588524,2
RP2040,U3,RP2040-QFN-56,C2040,1
SW_Push,"SW_ESP_BOOTSEL1,SW_ESP_RESET1,SW_RP_BOOTSEL1,SW_RP_RESET1",SW_SPST_TS-1088-xR020,C720477,4
W25Q128JVS,U1,SOIC-8_5.3x5.3mm_P1.27mm,C97521,1

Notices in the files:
README.md:
Firmware: GPL-3.0
Hardware: CC BY-NC 4.0
